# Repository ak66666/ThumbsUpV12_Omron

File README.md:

# ThumbsUp! v12 RP2040-based ProMicro 3x12 chord keyboard for Omron and mouse switches.
                           
Steno/chord keyboard (number key instead of a bar)
2-key Thumb Cluster
Cirque ProGlide trackpad/touchpad

Omron mouse switches or 6x6 two-pin switches.

* RP2040 ProMicro x2
* TRS (3-wire) audio cable to connect the halves.
* USB-C connectors.

Silicone O-rings are used for the key paddles suspension: CS2.4mm, OD 11mm (12mm works too).
Cross section 2-2.5 mm works well.
OD less than 11mm result in much heavier keys. 
OD more than 12mm is a bit too loose.

# Curvy Case for Rev.5 and Rev.6

Added a drop-in case for rev.5 and rev.6 boards (they have the same outline):
File: "...\3D Printed\Rev.5\v12 rev5 Curvy Case Left.stl"

# Rev.6

Made the thumb keys reverseable - their hinges were separated from the top keys/trackpad cover.
That little two-key hinge could be placed closer to the front edge, in somewhat return to the rev.0/rev.1 layout.
Otherwise it is the same as rev.5

Reversed keys are more comfortable when the board is below elbows level, but placed on the desk thumb keys are hard to reach.
So, not sure if it much better than rev.5 with the thumbs reversed.
With the front-facing thumb pads they are the same, and the top row board is stronger with the wobbly hook cut off.

# Rev.5

Re-worked the cross-board connections: 
Replaced the mix of pin headers/sockets and stand-offs with individual stand-off for each key, plus one in a corner.
This way the boards should stay flat, no twisting due to minor height mismatch and the connectors pulled upwards unevenly.
Hopefully that will equalize the key reactions, uniform the feel.

Split the top board in two parts - to move the thumb keys higher and a bit closer to the index finger column. 
If it was left as a single detail - it would be C-shaped board with a thin profile, could be easily broken, and, probably, harder to manufacture and deliver.

Moved the MCU, connectors to make room for the stand-offs, re-laid the tracks where affected.

# Rev.4

Moved the keys as in rev.1, as the rev.3 inherited the spacing from rev.2 and was a bit uncomfortable.

# Rev.3

Approx. 15g activation with Omron switches, reduced from the previous revisions.
Cirque ProGlide trackpad support - on both or one of the sides.
Handiness pin added.

# Rev.2

# Rev.1

Other pictures and videos in Photos folder.

# Firmware

TX-Bolt interface as the only connectivity option for now:
https://github.com/ak66666/qmk_firmware/tree/thumbsup_20240523/keyboards/thumbsup/rev12_rp2040_split_steno

# Javelin

Loaded Javelin to this v12 rev.5/6 and v13:
https://github.com/ak66666/javelin-steno-pico

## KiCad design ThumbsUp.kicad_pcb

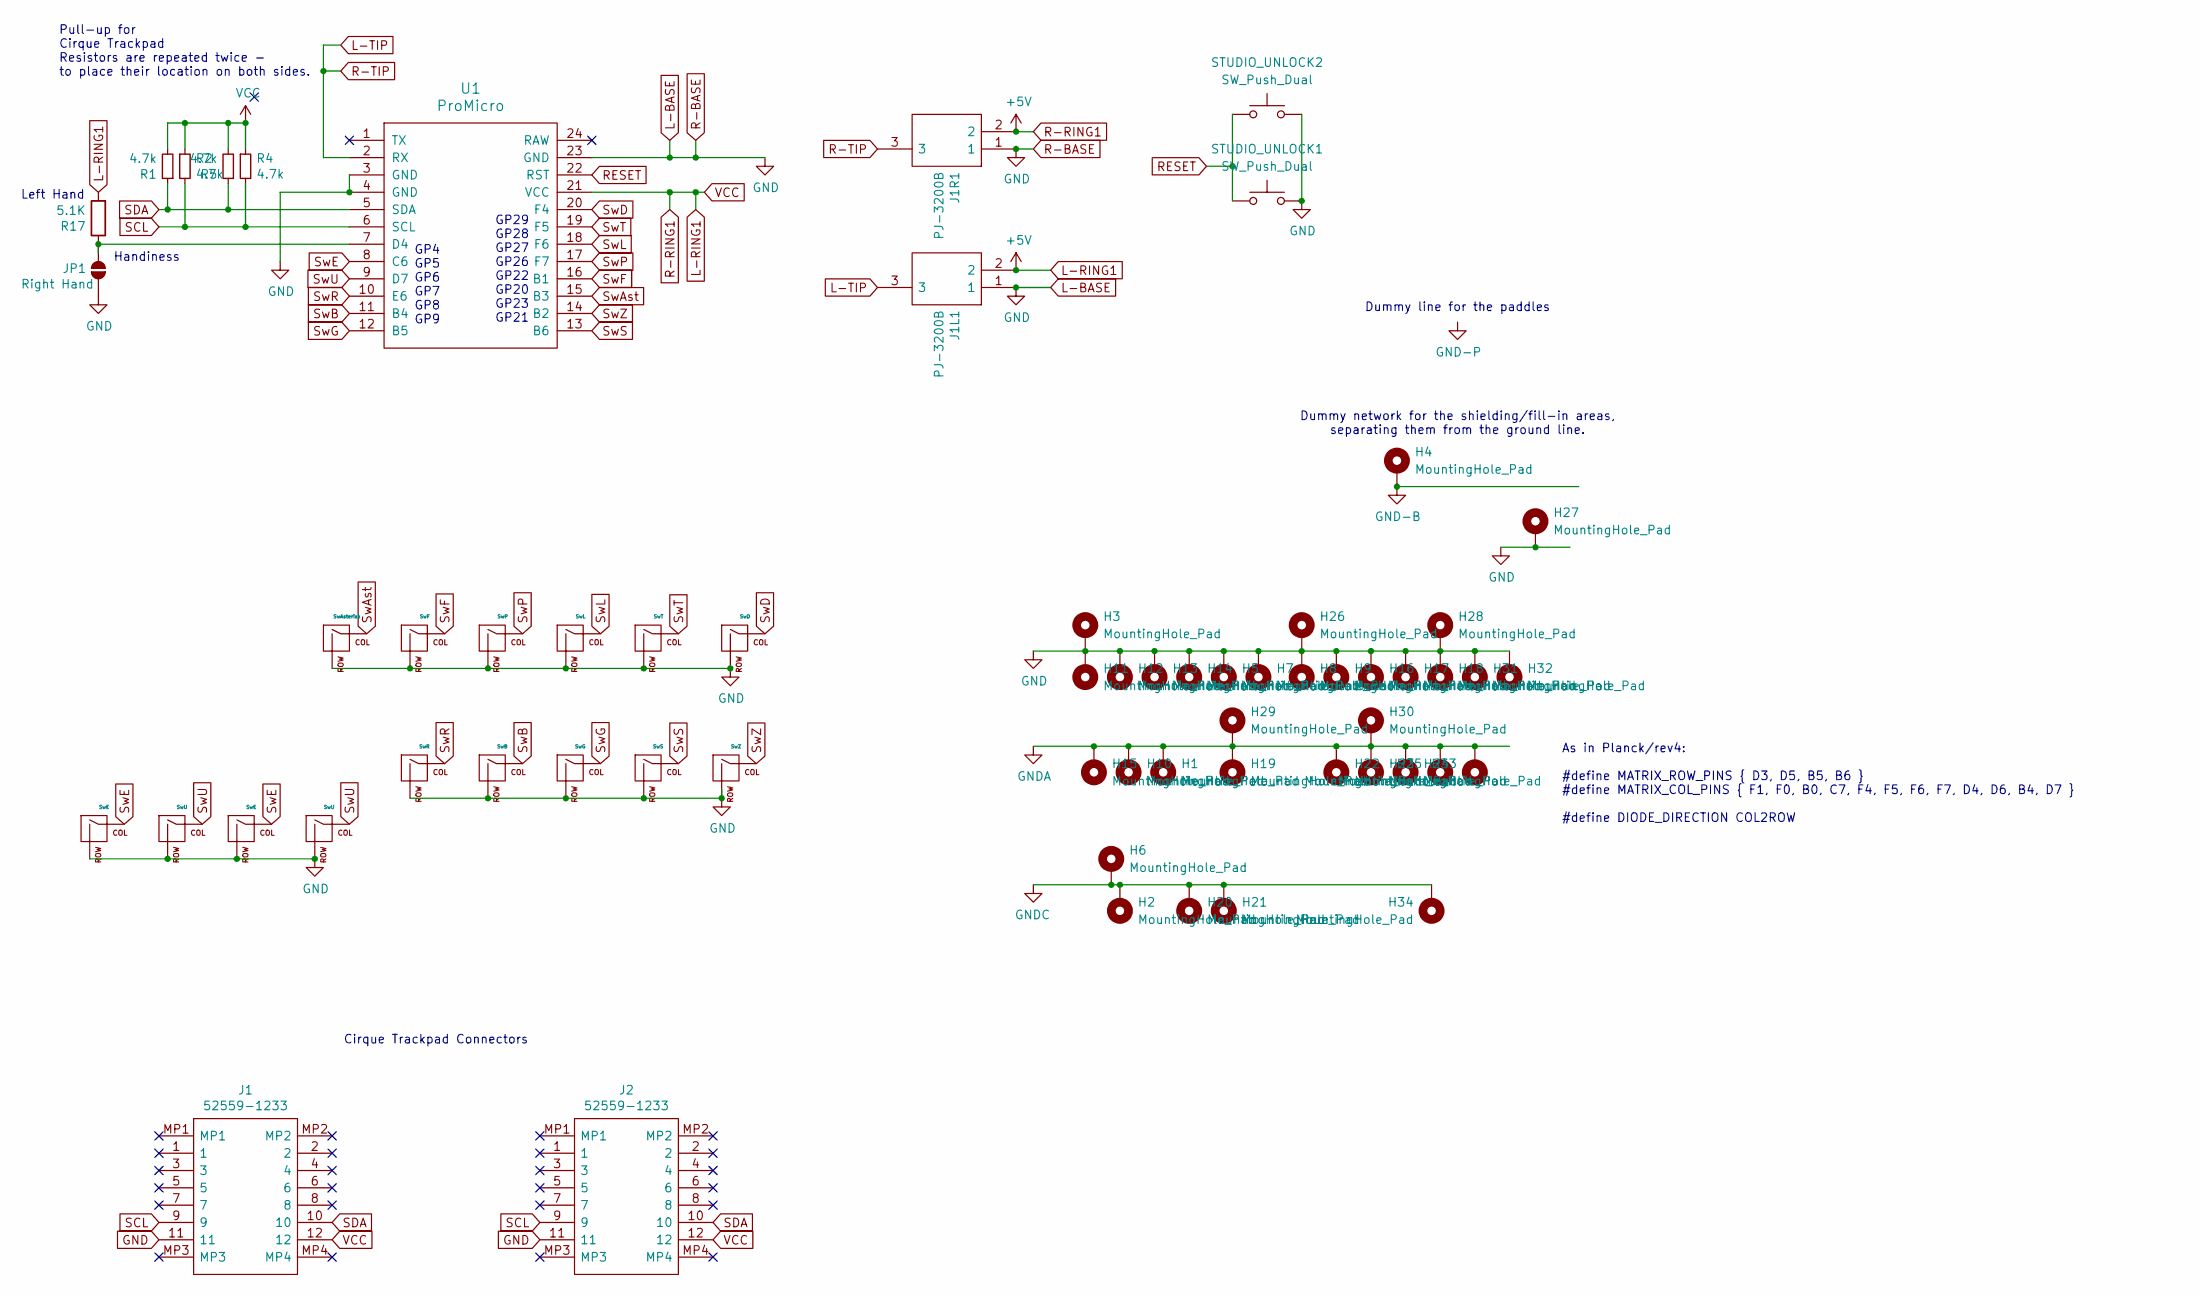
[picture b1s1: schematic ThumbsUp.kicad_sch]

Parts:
H1, H2, H3, H5, H6, H7, H8, H9, H10, H11, H12, H13, H14, H15, H16, H17, H18, H19, H20, H21, H22, H23, H24, H25, H26, H27, H28, H29, H30, H31, H32, H33, H34: MountingHole_Pad; MountingHole_3.5mm_Pad
H4: MountingHole_Pad; MountingHole_4.5mm_Pad
J1, J2: 52559-1233; 525591233; Mouser Part Number 538-52559-1233
J1L1, J1R1: PJ-3200B; PJ-3200B-4A; Manufacturer_Part_Number STX-3501-3N; Mouser Part Number 806-STX-3501-3N
JP1: Right Hand; SolderJumper-2_P1.3mm_Open_RoundedPad1.0x1.5mm
MX1, MX30: SwE; SW_D2FC_OMR
MX2, MX26: SwU; SW_D2FC_OMR
MX23: SwAsterisk; SW_D2FC_OMR
MX27: SwF; SW_D2FC_OMR
MX28: SwR; SW_D2FC_OMR
MX31: SwP; SW_D2FC_OMR
MX32: SwB; SW_D2FC_OMR
MX35: SwL; SW_D2FC_OMR
MX36: SwG; SW_D2FC_OMR
MX39: SwT; SW_D2FC_OMR
MX40: SwS; SW_D2FC_OMR
MX42: SwD; SW_D2FC_OMR
MX43: SwZ; SW_D2FC_OMR
R1, R2, R4, R5: 4.7k; R_0805_2012Metric
R17: 5.1K; R_0805_2012Metric
STUDIO_UNLOCK1, STUDIO_UNLOCK2: SW_Push_Dual; SW_Push_1P1T_NO_CK_KSC6xxJ
U1: ProMicro; ProMicro-NoSilk

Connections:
GND: H3.1, H5.1, H7.1, H8.1, H9.1, H11.1, H12.1, H13.1, H14.1, H16.1, H17.1, H18.1, H26.1, H27.1, H28.1, H31.1, H32.1, J1.11, J1L1.1, J1R1.1, J2.11, JP1.1 (A), MX1.2 (ROW), MX2.2 (ROW), MX23.2 (ROW), MX26.2 (ROW), MX27.2 (ROW), MX28.2 (ROW), MX30.2 (ROW), MX31.2 (ROW), MX32.2 (ROW), MX35.2 (ROW), MX36.2 (ROW), MX39.2 (ROW), MX40.2 (ROW), MX42.2 (ROW), MX43.2 (ROW), STUDIO_UNLOCK1.2, STUDIO_UNLOCK2.2, U1.3 (GND), U1.4 (GND), U1.23 (GND)
GND-B: H4.1
GNDA: H1.1, H10.1, H15.1, H19.1, H22.1, H23.1, H24.1, H25.1, H29.1, H30.1, H33.1
GNDC: H2.1, H6.1, H20.1, H21.1, H34.1
L-RING1: J1.12, J1L1.2, J1R1.2, J2.12, R1.2, R2.1, R4.1, R5.2, R17.2, U1.21 (VCC)
L-TIP: J1L1.3, J1R1.3, U1.2 (RX)
unnamed: JP1.2 (B), R17.1, U1.7 (D4)
RESET: STUDIO_UNLOCK1.1, STUDIO_UNLOCK2.1, U1.22 (RST)
SCL: J1.9, J2.9, R2.2, R4.2, U1.6 (SCL)
SDA: J1.10, J2.10, R1.1, R5.1, U1.5 (SDA)
SwAst: MX23.1 (COL), U1.15 (B3)
SwB: MX32.1 (COL), U1.11 (B4)
SwD: MX42.1 (COL), U1.20 (F4)
SwE: MX1.1 (COL), MX30.1 (COL), U1.8 (C6)
SwF: MX27.1 (COL), U1.16 (B1)
SwG: MX36.1 (COL), U1.12 (B5)
SwL: MX35.1 (COL), U1.18 (F6)
SwP: MX31.1 (COL), U1.17 (F7)
SwR: MX28.1 (COL), U1.10 (E6)
SwS: MX40.1 (COL), U1.13 (B6)
SwT: MX39.1 (COL), U1.19 (F5)
SwU: MX2.1 (COL), MX26.1 (COL), U1.9 (D7)
SwZ: MX43.1 (COL), U1.14 (B2)

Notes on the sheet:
Pull-up for Cirque Trackpad Resistors are repeated twice - to place their location on both sides.
As in Planck/rev4: #define MATRIX_ROW_PINS { D3, D5, B5, B6 } #define MATRIX_COL_PINS { F1, F0, B0, C7, F4, F5, F6, F7, D4, D6, B4, D7 } #define DIODE_DIRECTION COL2ROW
Cirque Trackpad Connectors
GP4 GP5 GP6 GP7 GP8 GP9
GP29 GP28 GP27 GP26 GP22 GP20 GP23 GP21
Left Hand
Dummy line for the paddles
Handiness
Dummy network for the shielding/fill-in areas, separating them from the ground line.

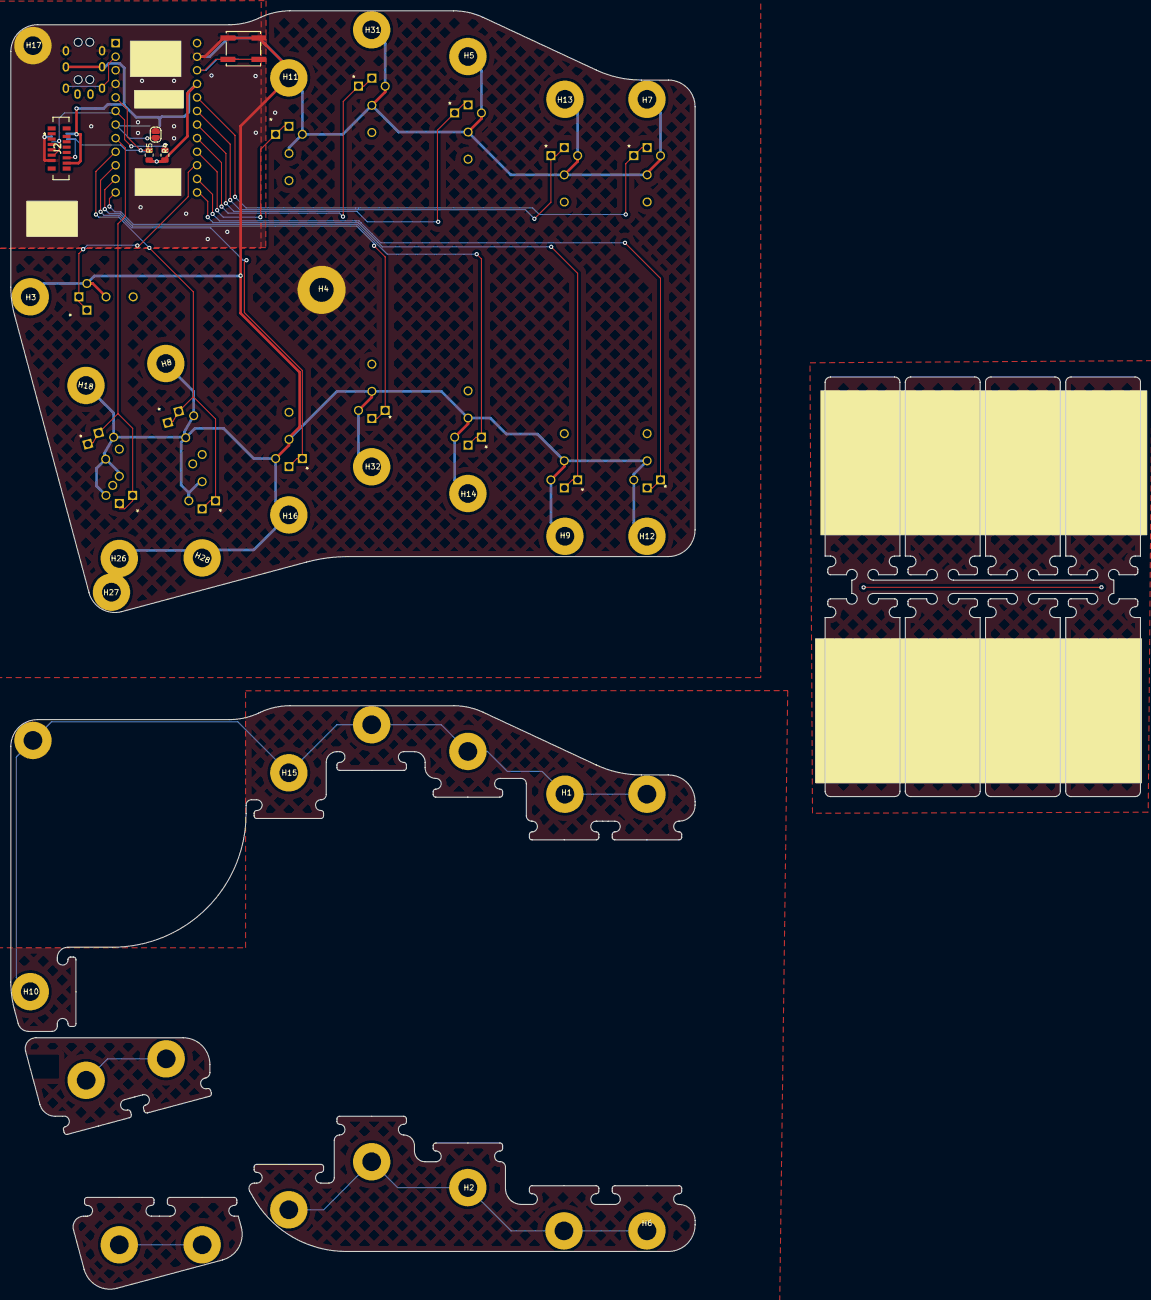
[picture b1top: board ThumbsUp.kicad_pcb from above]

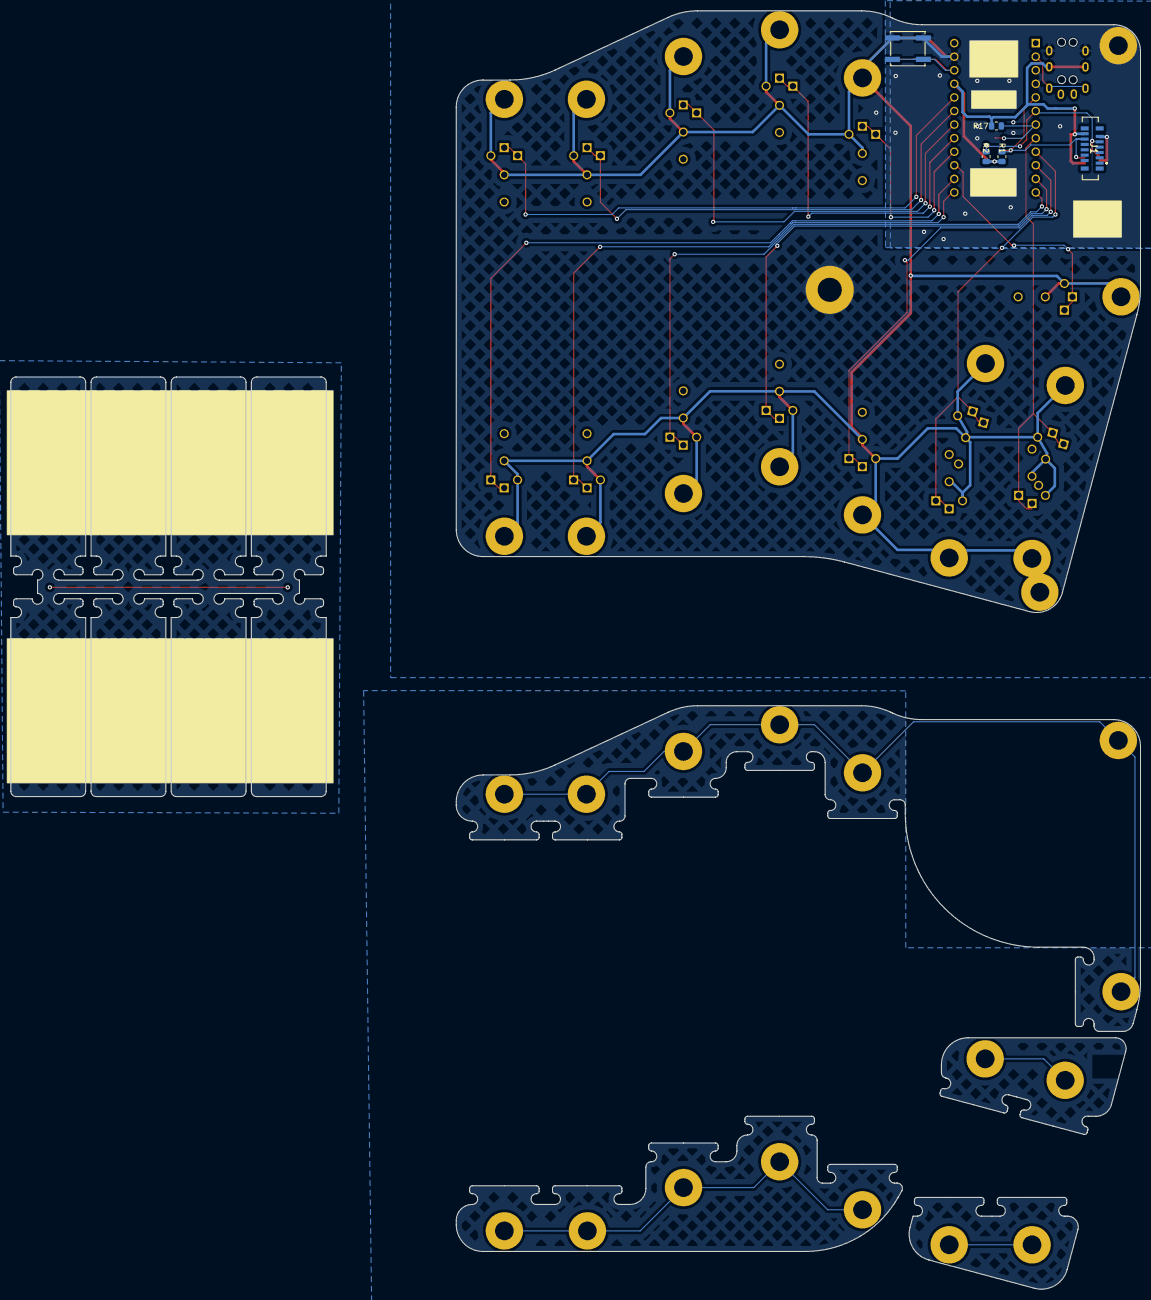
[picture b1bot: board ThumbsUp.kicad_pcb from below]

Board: 2 copper layers, 211.3 x 239.2 mm, 62 parts (6 on the bottom side), 22 nets.

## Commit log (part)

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2025-12-10 K12: First outline
2025-12-10 K12: Draft schematics, initial physical layout.
2025-12-11 K12: Before splitting the boards.
2025-12-11 K12: Before generating Kerbers.
2025-12-11 K12: As ordered 2025-12-10
2025-12-11 K12: Added a mounting hole. Moved the tracks a bit. Haven't modified the gerbers
2025-12-28 K12: Modifying the layout, WIP.
2026-01-02 K12: Regenerated gerbers, as ordered 20260101.
2026-01-02 K12: Added photos, videos of rev.0.
2026-01-02 K12: Corrected readme.md to reflect the project.
2026-01-21 K12: rev.1 with pictures.
2026-01-26 K12: New switch supports - tilted.
2026-01-27 K12: Changed layout as per rev.1 usage experience.
2026-01-27 K12: Added left-side handiness pull-up R, laid out all tracks. TODO: generate Gerbers.
2026-01-28 K12: Gerbers generated. As ordered 20260127.
2026-02-10 K12: Added photos of rev.1 with Omron switches.
2026-02-11 K12: Added a tilted/tented base.
2026-03-05 K12: Doing modifications outlined for rev.3
2026-03-05 K12: Placed the touchpad, todo: tracks
2026-03-06 K12: Placed the tracks, text, etc. TODO: generate Gerbers.
2026-03-07 K12: Moved the thumb keys a bit up, closer to the fingers. TODO: generate Gerbers.
2026-03-07 K12: Added Gerbers as ordered 20260306.
2026-03-14 K12: Added pictures of rev.3.
2026-03-14 K12: Updated description.
2026-03-17 K12: Moved the pinkie cluster 4mm out, 3mm down.//TODO: generate Gerbers
2026-03-17 K12: Moved the top border a bit to thicken the bridge between -L and -T. Shuffled the stand-offs and headers around to space them more evenly.//TODO: generate Gerbers
2026-03-17 K12: Recreated Gerbers. As Ordered 20260317.
2026-06-02 v12: Replaced pin headers/sockets with stand-offs..
2026-06-10 v12: Moving the thumb keys around.
2026-06-11 v12: Added stand-offs instead of pin headers/sockets.
2026-06-11 v12: Minor corrections.
2026-06-11 v12: Cleaned up orphaned tracks, prepared for Gerbers generation..
2026-06-11 v12: Prepared Gerbers as ordered 2026-06-11.
2026-06-11 v12: Updated description.
